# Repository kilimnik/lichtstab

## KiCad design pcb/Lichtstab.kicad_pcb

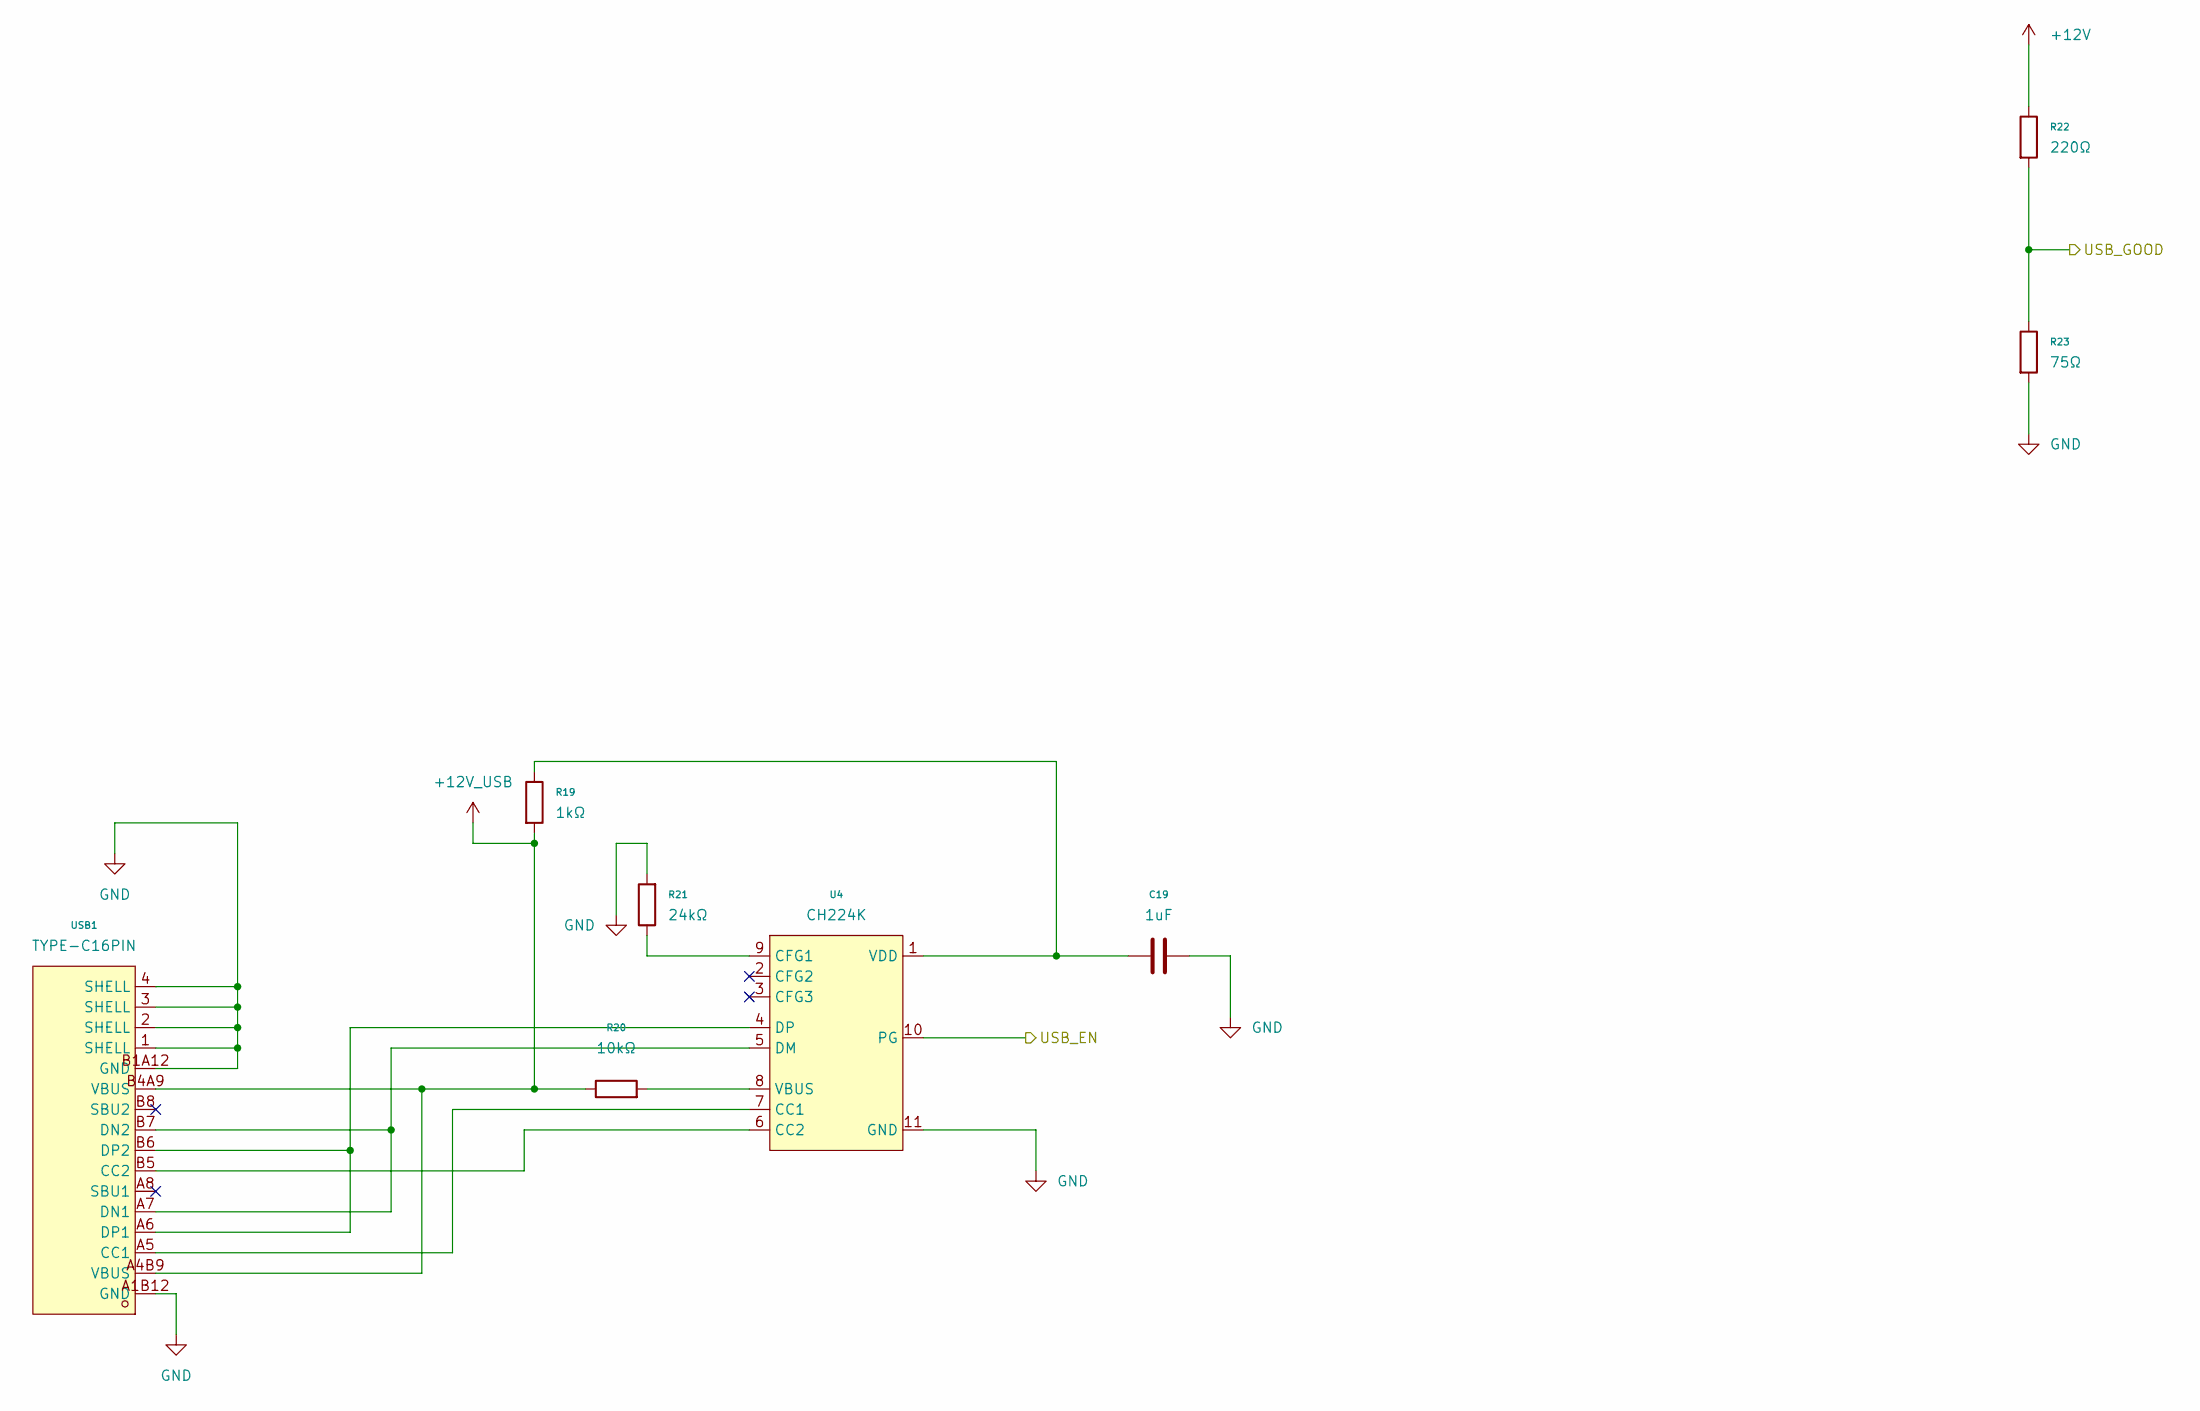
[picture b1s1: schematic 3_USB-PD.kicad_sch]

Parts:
C19: 1uF; C_0805_2012Metric; LCSC C28323
R19: 1kΩ; R_0603_1608Metric; LCSC C21190
R20: 10kΩ; R_0603_1608Metric; LCSC C25804
R21: 24kΩ; R_0603_1608Metric; LCSC C23352
R22: 220Ω; R_0603_1608Metric; LCSC C22962
R23: 75Ω; R_0603_1608Metric; LCSC C4275
U4: CH224K; ESSOP-10_L4.9-W3.9-P1.0-LS6.0-TL-EP; LCSC C970725
USB1: TYPE-C16PIN; USB-C-SMD_TYPE-C16PIN; LCSC C393939

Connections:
+12V: R22.1; also elsewhere on the board
+12V_USB: R19.2, R20.1, USB1.A4B9 (VBUS), USB1.B4A9 (VBUS); also elsewhere on the board
/General/ESP_EN: U4.10 (PG); also elsewhere on the board
/General/USB_GOOD: R22.2, R23.1; also elsewhere on the board
GND: C19.1, R21.2, R23.2, U4.11 (GND), USB1.1 (SHELL), USB1.2 (SHELL), USB1.3 (SHELL), USB1.4 (SHELL), USB1.A1B12 (GND), USB1.B1A12 (GND); also elsewhere on the board
unnamed: U4.7 (CC1), USB1.A5 (CC1)
unnamed: U4.6 (CC2), USB1.B5 (CC2)
unnamed: R21.1, U4.9 (CFG1)
unnamed: U4.5 (DM), USB1.A7 (DN1), USB1.B7 (DN2)
unnamed: U4.4 (DP), USB1.A6 (DP1), USB1.B6 (DP2)
unnamed: R20.2, U4.8 (VBUS)
unnamed: C19.2, R19.1, U4.1 (VDD)

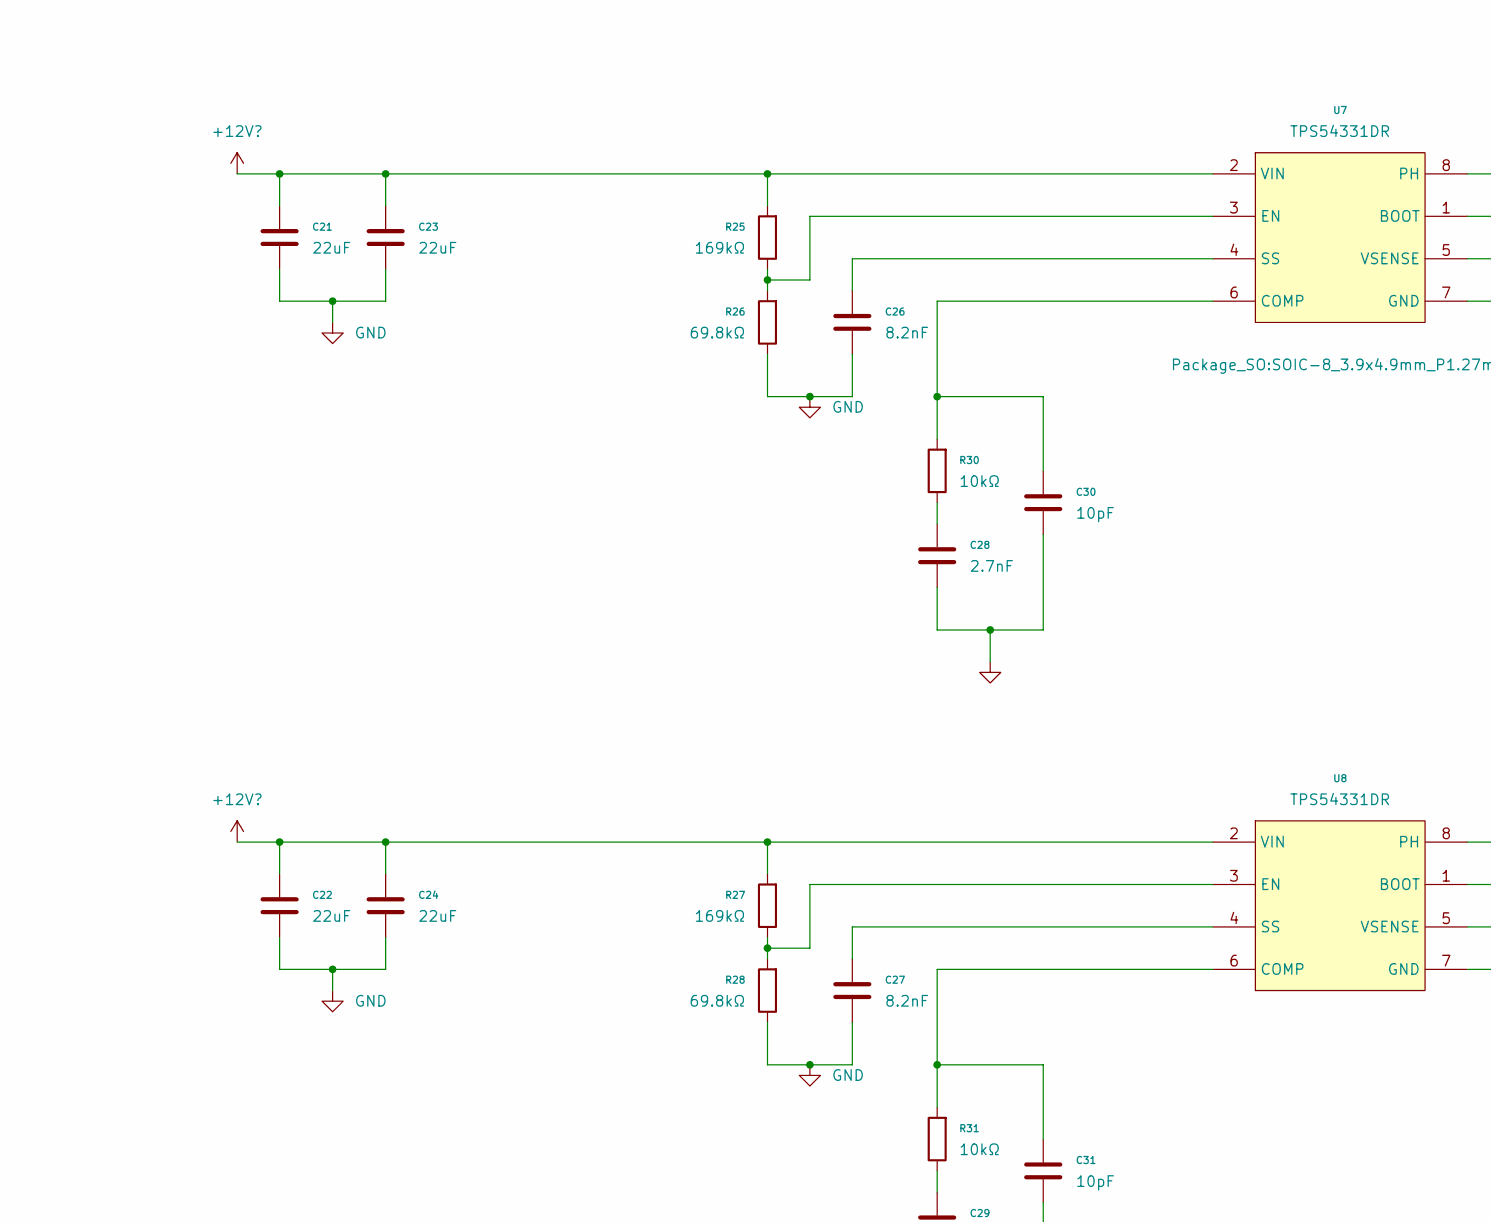
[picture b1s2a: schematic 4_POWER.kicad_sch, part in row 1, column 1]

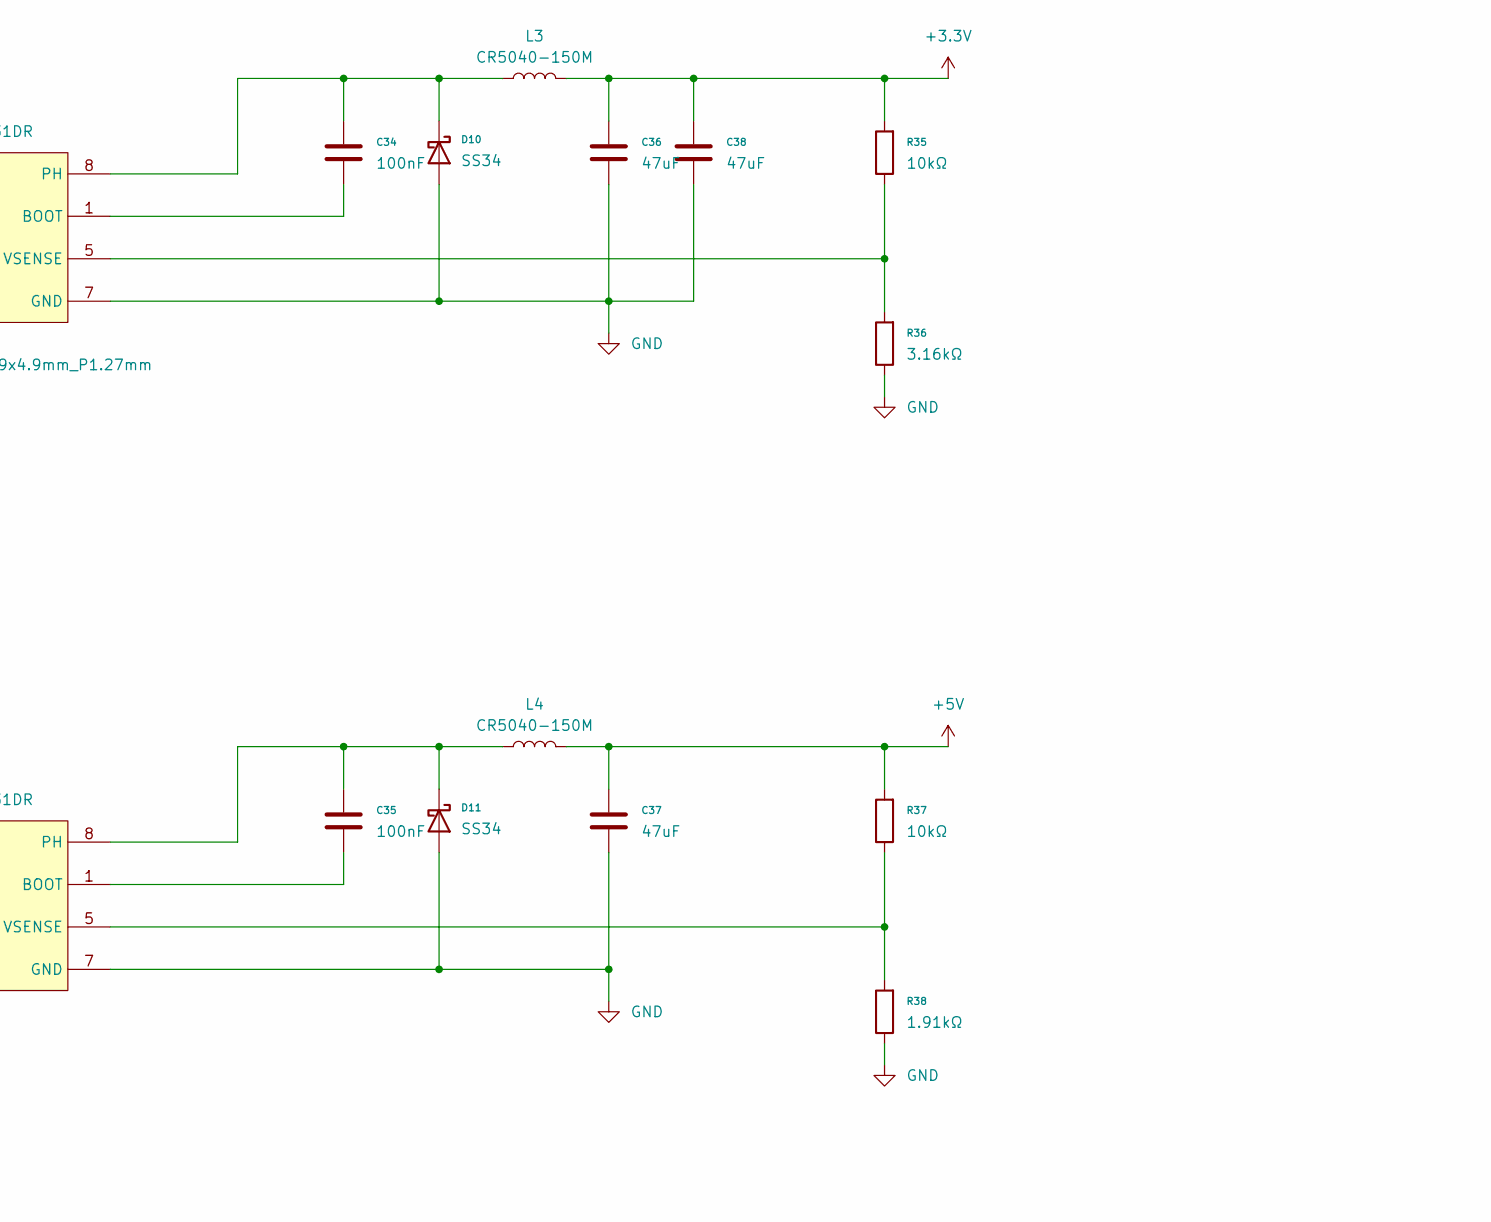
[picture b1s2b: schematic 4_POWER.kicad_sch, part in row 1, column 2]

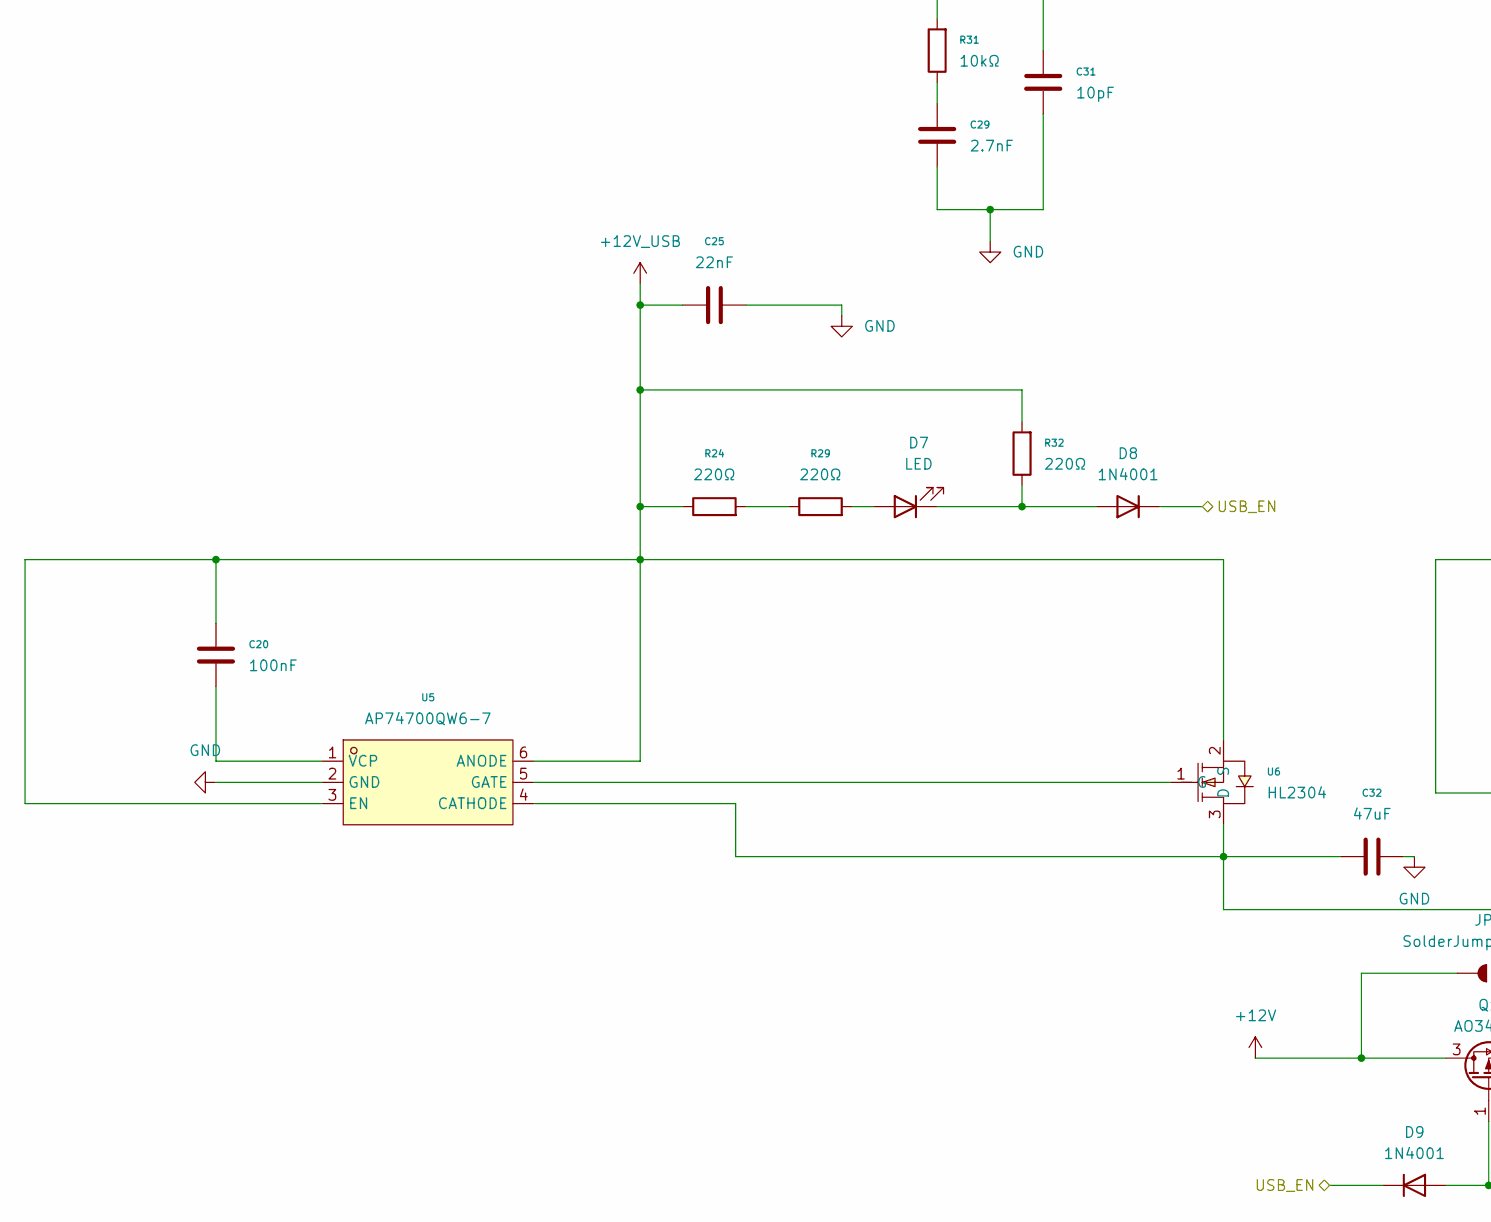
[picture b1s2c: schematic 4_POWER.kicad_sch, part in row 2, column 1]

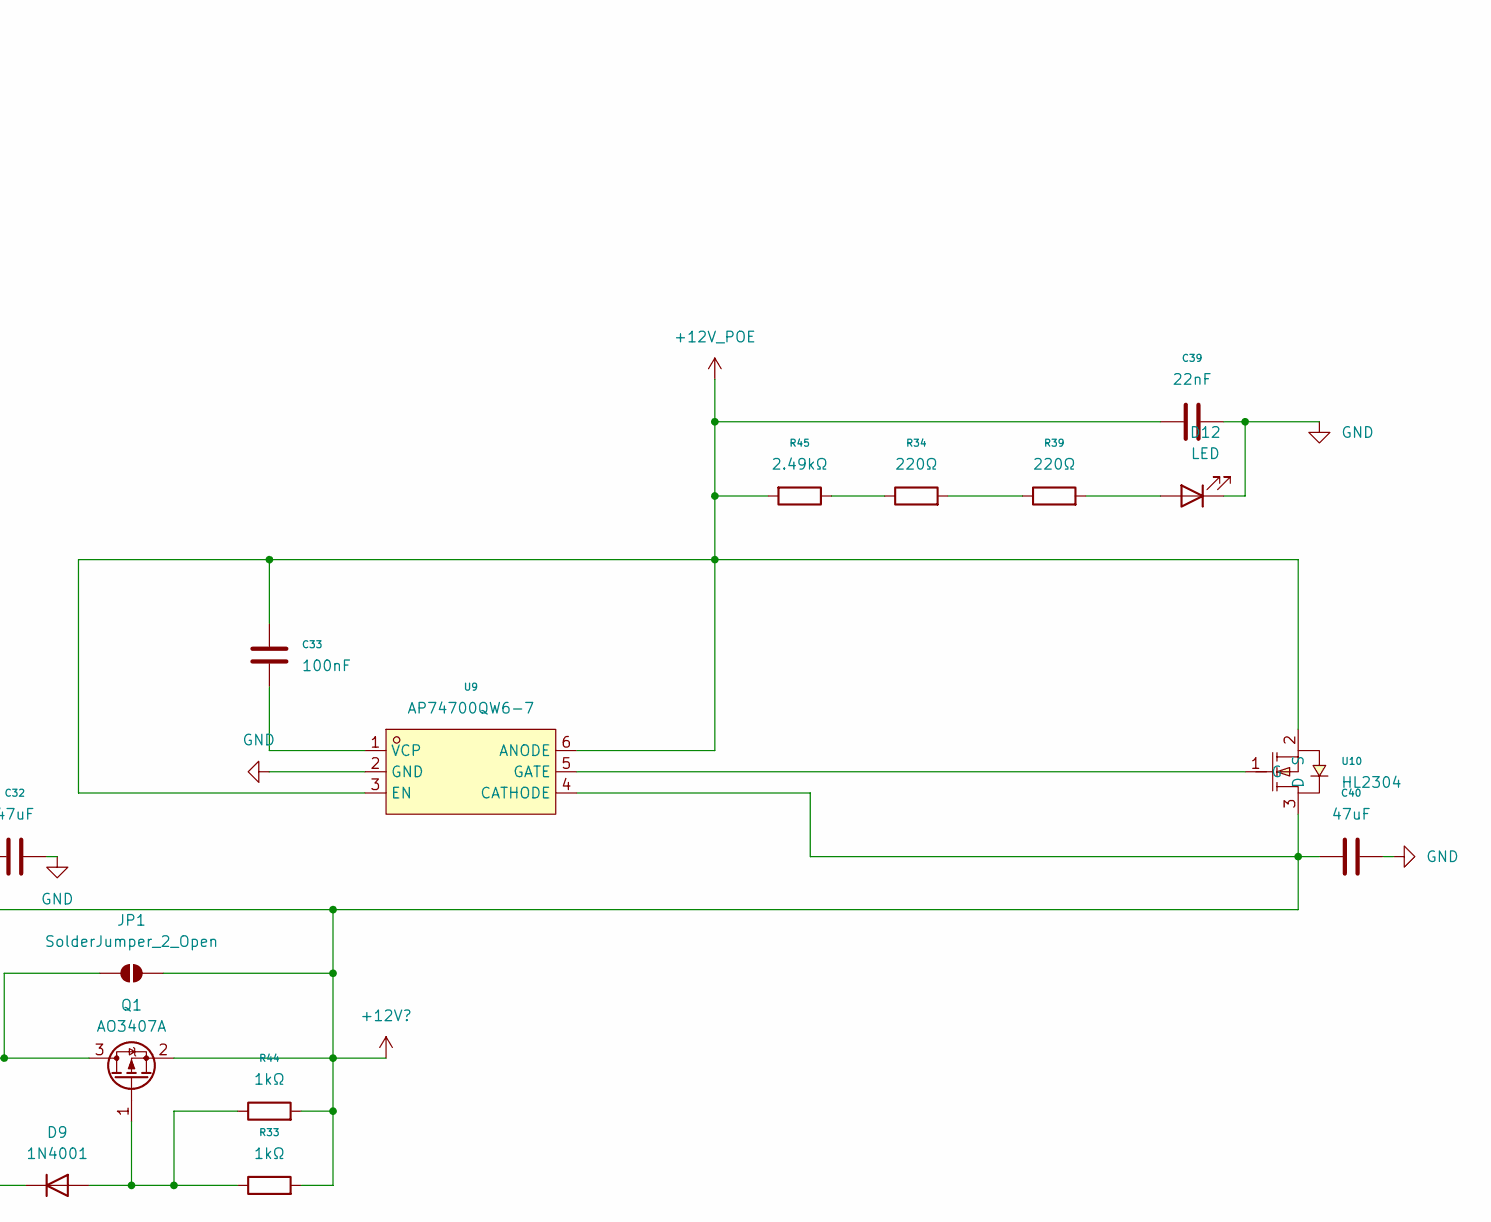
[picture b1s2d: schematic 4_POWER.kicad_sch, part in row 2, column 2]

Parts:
C20, C33, C34, C35: 100nF; C_0603_1608Metric; LCSC C14663
C21, C22, C23, C24: 22uF; C_1210_3225Metric; LCSC C2918506
C25, C39: 22nF; C_0603_1608Metric; LCSC C21122
C26, C27: 8.2nF; C_0603_1608Metric; LCSC C1322360
C28, C29: 2.7nF; C_0805_2012Metric; LCSC C5186791
C30, C31: 10pF; C_0805_2012Metric; LCSC C157608
C32, C36, C37, C38, C40: 47uF; C_1206_3216Metric; LCSC C22367835
D7, D12: LED; LED_0805_2012Metric; LCSC C2297
D8, D9: 1N4001; D_SOD-123F; LCSC C2892326
D10, D11: SS34; D_SMA; LCSC C8678
JP1: SolderJumper_2_Open; SolderJumper-2_P1.3mm_Open_TrianglePad1.0x1.5mm
L3, L4: CR5040-150M; IND-SMD_L5.0-W5.0_SWPA5040S; LCSC Part C520353
Q1: AO3407A; SOT-23; LCSC C347478
R24, R29, R32, R34, R39: 220Ω; R_0603_1608Metric; LCSC C22962
R25, R27: 169kΩ; R_0603_1608Metric; LCSC C22817
R26, R28: 69.8kΩ; R_0603_1608Metric; LCSC C23098
R30, R31, R35, R37: 10kΩ; R_0603_1608Metric; LCSC C25804
R33, R44: 1kΩ; R_0603_1608Metric; LCSC C21190
R36: 3.16kΩ; R_0603_1608Metric; LCSC C22993
R38: 1.91kΩ; R_0603_1608Metric; LCSC C22853
R45: 2.49kΩ; R_0603_1608Metric; LCSC C22908
U5, U9: AP74700QW6-7; SOT-23-6; LCSC C5381661
U6, U10: HL2304; SOT-23; LCSC C7420346
U7, U8: TPS54331DR; SOIC-8_3.9x4.9mm_P1.27mm; LCSC C9865

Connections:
+3.3V: C36.1, C38.1, L3.2, R35.2; also elsewhere on the board
+5V: C37.2, L4.2, R37.2; also elsewhere on the board
+12V: JP1.1 (A), Q1.3 (D); also elsewhere on the board
+12V?: C21.2, C22.2, C23.2, C24.2, C32.1, C40.1, JP1.2 (B), Q1.2 (S), R25.2, R27.2, R33.2, R44.2, U5.4 (CATHODE), U6.3 (D), U7.2 (VIN), U8.2 (VIN), U9.4 (CATHODE), U10.3 (D)
+12V_POE: C33.1, C39.1, R45.2, U9.3 (EN), U9.6 (ANODE), U10.2 (S); also elsewhere on the board
+12V_USB: C20.1, C25.1, R24.1, R32.2, U5.3 (EN), U5.6 (ANODE), U6.2 (S); also elsewhere on the board
/General/ESP_EN: D8.1 (K), D9.1 (K); also elsewhere on the board
GND: C21.1, C22.1, C23.1, C24.1, C25.2, C26.1, C27.1, C28.1, C29.1, C30.1, C31.1, C32.2, C36.2, C37.1, C38.2, C39.2, C40.2, D10.2 (A), D11.2 (A), D12.1 (K), R26.1, R28.1, R36.1, R38.1, U5.2 (GND), U7.7 (GND), U8.7 (GND), U9.2 (GND); also elsewhere on the board
unnamed: C28.2, R30.1
unnamed: C29.2, R31.1
unnamed: D7.2 (A), R29.2
unnamed: D7.1 (K), D8.2 (A), R32.1
unnamed: D9.2 (A), Q1.1 (G), R33.1, R44.1
unnamed: C34.1, D10.1 (K), L3.1, U7.8 (PH)
unnamed: C35.1, D11.1 (K), L4.1, U8.8 (PH)
unnamed: D12.2 (A), R39.2
unnamed: R24.2, R29.1
unnamed: R34.1, R45.1
unnamed: R34.2, R39.1
unnamed: U5.5 (GATE), U6.1 (G)
unnamed: C20.2, U5.1 (VCP)
unnamed: C34.2, U7.1 (BOOT)
unnamed: C30.2, R30.2, U7.6 (COMP)
unnamed: R25.1, R26.2, U7.3 (EN)
unnamed: C26.2, U7.4 (SS)
unnamed: R35.1, R36.2, U7.5 (VSENSE)
unnamed: C35.2, U8.1 (BOOT)
unnamed: C31.2, R31.2, U8.6 (COMP)
unnamed: R27.1, R28.2, U8.3 (EN)
unnamed: C27.2, U8.4 (SS)
unnamed: R37.1, R38.2, U8.5 (VSENSE)
unnamed: C33.2, U9.1 (VCP)
unnamed: U9.5 (GATE), U10.1 (G)

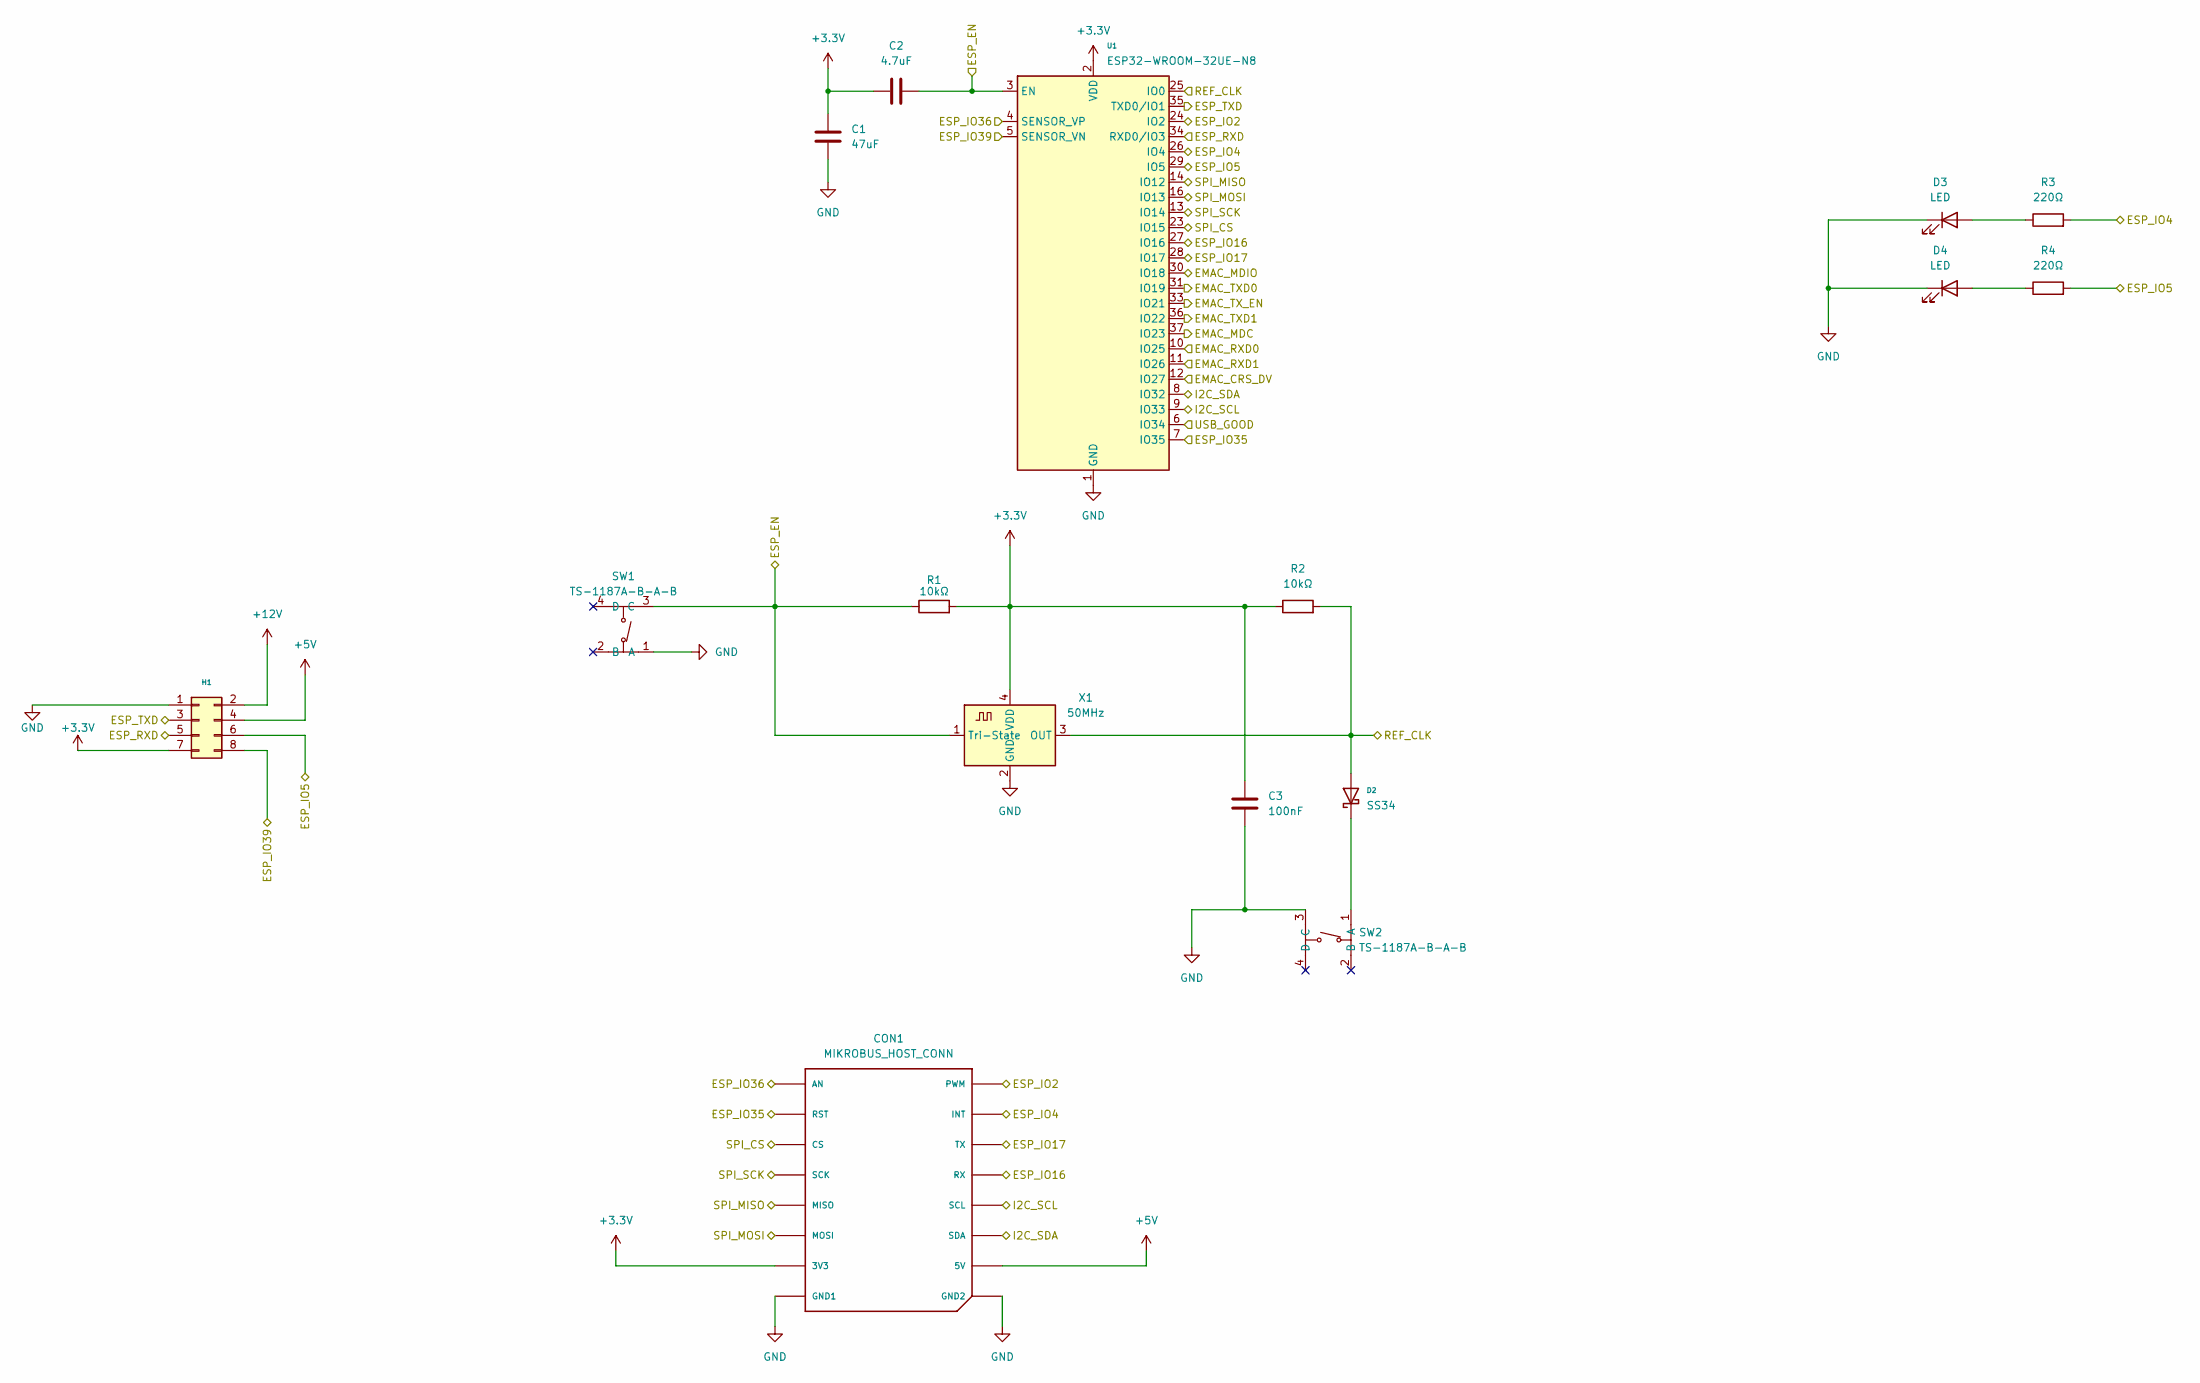
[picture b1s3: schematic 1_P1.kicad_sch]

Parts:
C1: 47uF; C_1206_3216Metric; LCSC C22367835
C2: 4.7uF; C_0603_1608Metric
C3: 100nF; C_0603_1608Metric
CON1: MIKROBUS_HOST_CONN
D2: SS34; D_SMA; LCSC C8678
D3, D4: LED; LED_0805_2012Metric; LCSC C34499
H1: PinHeader_2x04_P2.54mm_Vertical_SMD; Manufacturer Part Programming Header; LCSC C192300
R1, R2: 10kΩ; R_0603_1608Metric
R3, R4: 220Ω; R_0603_1608Metric
SW1: TS-1187A-B-A-B; SW-SMD_4P-L5.1-W5.1-P3.70-LS6.5-TL-2; Manufacturer Part Reset Switch; LCSC C318884
SW2: TS-1187A-B-A-B; SW-SMD_4P-L5.1-W5.1-P3.70-LS6.5-TL-2; Manufacturer Part Boot Switch; LCSC C318884
U1: ESP32-WROOM-32UE-N8; ESP32-WROOM-32UE; LCSC C701345
X1: 50MHz; Crystal_SMD_3225-4Pin_3.2x2.5mm; LCSC C717684

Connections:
+3.3V: C1.1, C2.2, C3.1, CON1.P7 (3V3), H1.7, R1.2, R2.1, U1.2 (VDD), X1.4 (VDD); also elsewhere on the board
+5V: CON1.P10 (5V), H1.4; also elsewhere on the board
+12V: H1.2; also elsewhere on the board
/General/EMAC_CRS_DV: U1.12 (IO27); also elsewhere on the board
/General/EMAC_MDC: U1.37 (IO23); also elsewhere on the board
/General/EMAC_MDIO: U1.30 (IO18); also elsewhere on the board
/General/EMAC_RXD0: U1.10 (IO25); also elsewhere on the board
/General/EMAC_RXD1: U1.11 (IO26); also elsewhere on the board
/General/EMAC_TXD0: U1.31 (IO19); also elsewhere on the board
/General/EMAC_TXD1: U1.36 (IO22); also elsewhere on the board
/General/EMAC_TX_EN: U1.33 (IO21); also elsewhere on the board
/General/ESP_EN: C2.1, R1.1, SW1.3 (C), U1.3 (EN), X1.1 (Tri-State); also elsewhere on the board
/General/ESP_IO2: CON1.P16 (PWM), U1.24 (IO2); also elsewhere on the board
/General/ESP_IO4: CON1.P15 (INT), R3.2, U1.26 (IO4); also elsewhere on the board
/General/ESP_IO5: H1.6, R4.2, U1.29 (IO5); also elsewhere on the board
/General/ESP_IO16: CON1.P13 (RX), U1.27 (IO16); also elsewhere on the board
/General/ESP_IO17: CON1.P14 (TX), U1.28 (IO17); also elsewhere on the board
/General/ESP_IO35: CON1.P2 (RST), U1.7 (IO35); also elsewhere on the board
/General/ESP_IO36: CON1.P1 (AN), U1.4 (SENSOR_VP); also elsewhere on the board
/General/ESP_IO39: H1.8, U1.5 (SENSOR_VN); also elsewhere on the board
/General/ESP_RXD: H1.5, U1.34 (RXD0/IO3)
/General/ESP_TXD: H1.3, U1.35 (TXD0/IO1)
/General/I2C_SCL: CON1.P12 (SCL), U1.9 (IO33); also elsewhere on the board
/General/I2C_SDA: CON1.P11 (SDA), U1.8 (IO32); also elsewhere on the board
/General/REF_CLK: D2.2 (A), R2.2, U1.25 (IO0), X1.3 (OUT); also elsewhere on the board
/General/SPI_CS: CON1.P3 (CS), U1.23 (IO15); also elsewhere on the board
/General/SPI_MISO: CON1.P5 (MISO), U1.14 (IO12); also elsewhere on the board
/General/SPI_MOSI: CON1.P6 (MOSI), U1.16 (IO13); also elsewhere on the board
/General/SPI_SCK: CON1.P4 (SCK), U1.13 (IO14); also elsewhere on the board
/General/USB_GOOD: U1.6 (IO34); also elsewhere on the board
GND: C1.2, C3.2, CON1.P8 (GND1), CON1.P9 (GND2), D3.1 (K), D4.1 (K), H1.1, SW1.1 (A), SW2.3 (C), U1.1 (GND), U1.15 (GND), U1.38 (GND), U1.39 (GND), X1.2 (GND); also elsewhere on the board
unnamed: D2.1 (K), SW2.1 (A)
unnamed: D3.2 (A), R3.1
unnamed: D4.2 (A), R4.1

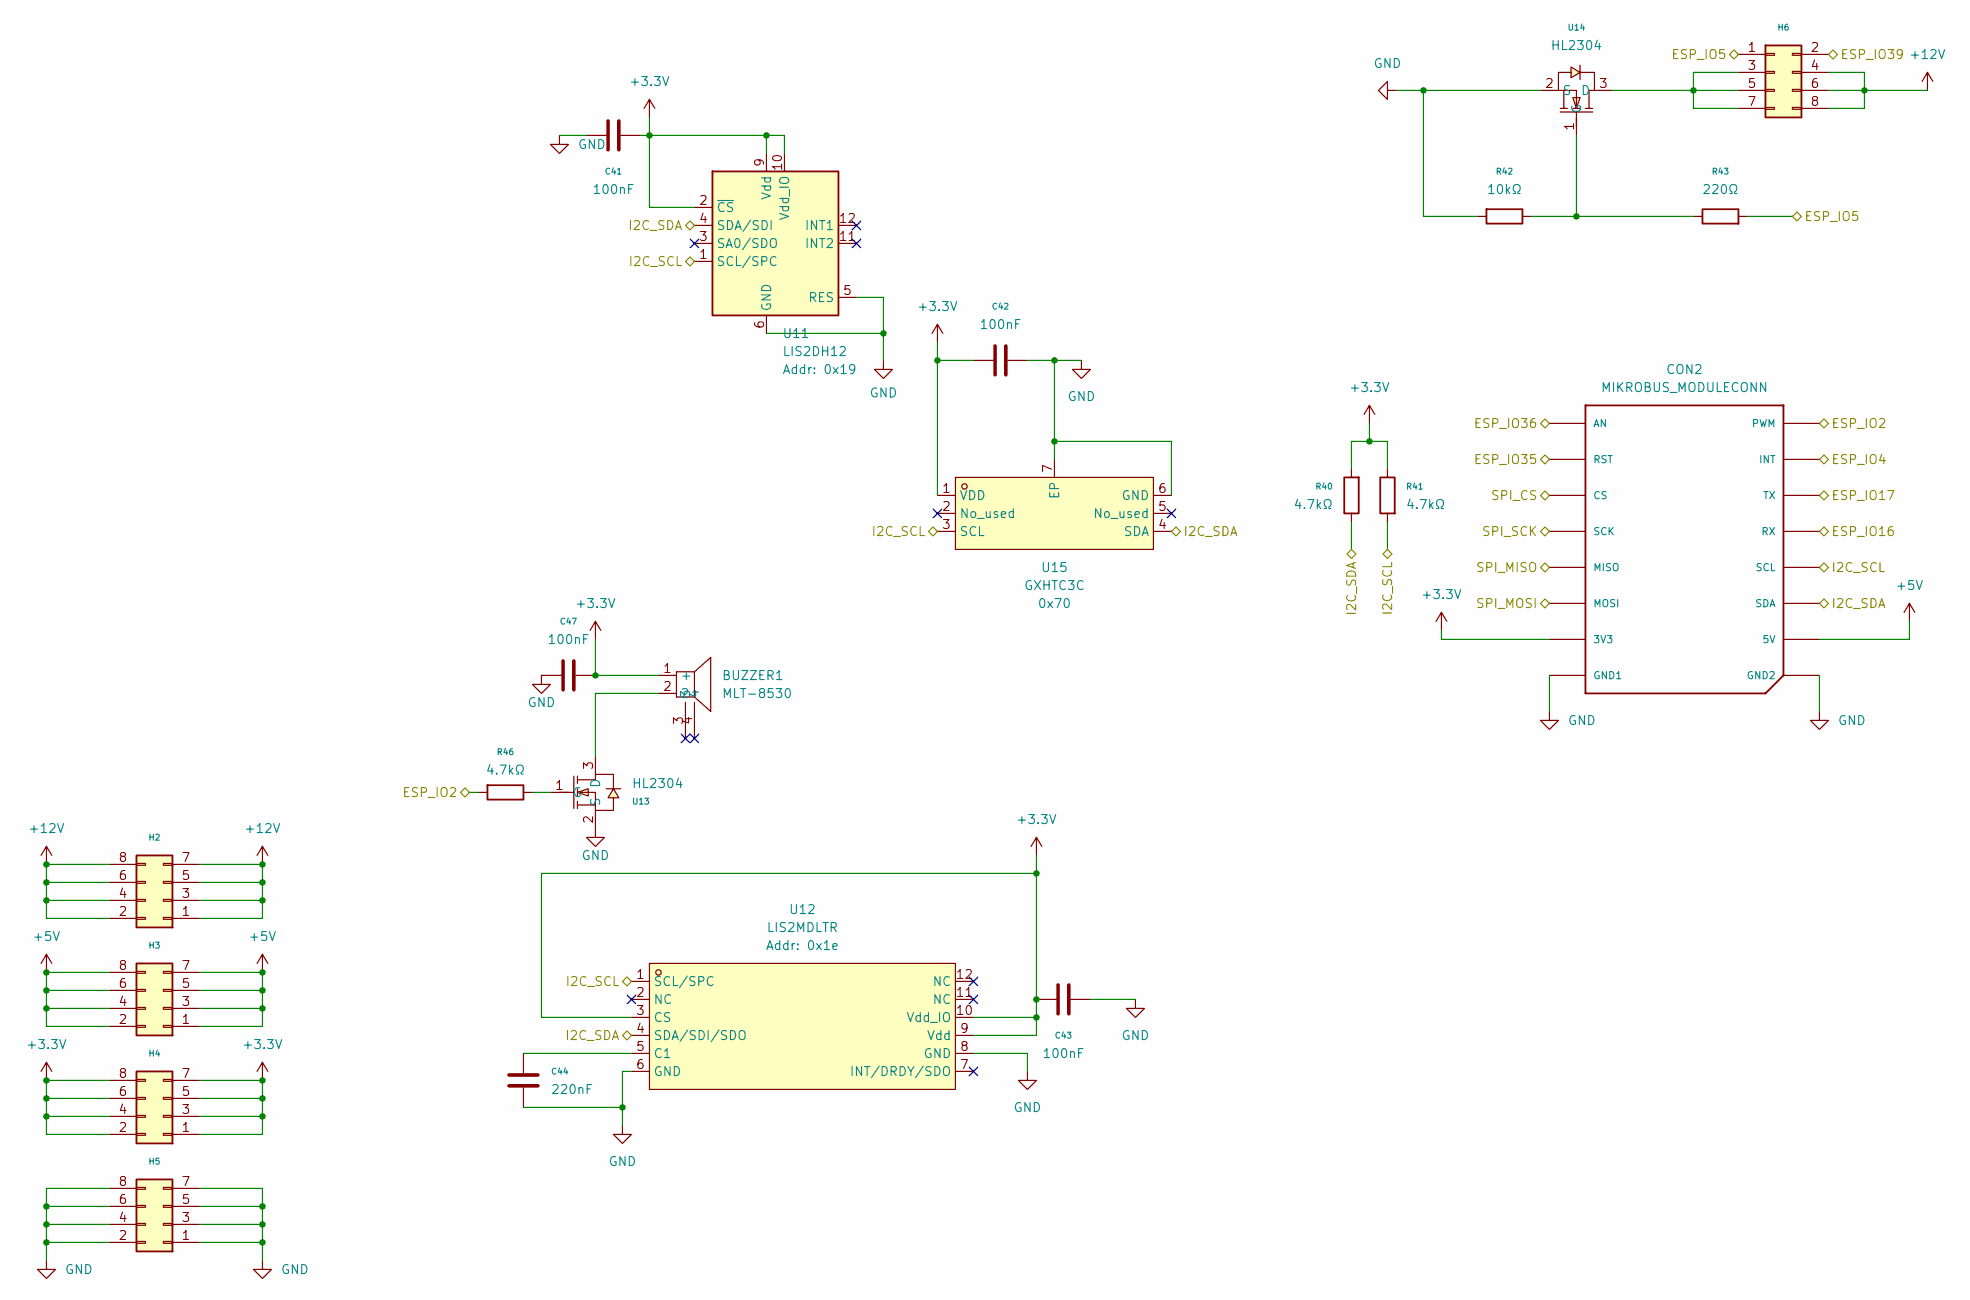
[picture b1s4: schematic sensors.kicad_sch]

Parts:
BUZZER1: MLT-8530; BUZ-SMD_4P-L8.5-W8.5-P8.50-BR; LCSC Part C94599
C41, C42, C43, C47: 100nF; C_0603_1608Metric; LCSC C14663
C44: 220nF; C_0603_1608Metric
CON2: MIKROBUS_MODULECONN; MIKROBUS_MODULE_CONN
H2: 2.54-2*4P立贴针; PinHeader_2x04_P2.54mm_Vertical_SMD; Manufacturer Part 12V Header; LCSC C192300
H3, H4: 2.54-2*4P立贴针; PinHeader_2x04_P2.54mm_Vertical_SMD; Manufacturer Part 3.3V Header; LCSC C192300
H5: 2.54-2*4P立贴针; PinHeader_2x04_P2.54mm_Vertical_SMD; Manufacturer Part GND Header; LCSC C192300
H6: 2.54-2*4P立贴针; PinHeader_2x04_P2.54mm_Vertical_SMD; Manufacturer Part Light Header; LCSC C192300
R40, R41, R46: 4.7kΩ; R_0603_1608Metric; LCSC C23162
R42: 10kΩ; R_0603_1608Metric; LCSC C25804
R43: 220Ω; R_0603_1608Metric; LCSC C22962
U11: LIS2DH12; LGA-12_2x2mm_P0.5mm; LCSC C110926
U12: LIS2MDLTR; LGA-12_L2.0-W2.0-P0.50-BL; LCSC C919695
U13, U14: HL2304; SOT-23; LCSC C7420346
U15: GXHTC3C; DFN-6_L2.0-W2.0-P0.50-TL-EP; LCSC Part C2913568

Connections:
+3.3V: BUZZER1.1 (+), C41.1, C42.2, C43.1, C47.1, CON2.P7 (3V3), H4.1, H4.2, H4.3, H4.4, H4.5, H4.6, H4.7, H4.8, R40.2, R41.1, U11.2 (~CS), U11.9 (Vdd), U11.10 (Vdd_IO), U12.3 (CS), U12.9 (Vdd), U12.10 (Vdd_IO), U15.1 (VDD); also elsewhere on the board
+5V: CON2.P10 (5V), H3.1, H3.2, H3.3, H3.4, H3.5, H3.6, H3.7, H3.8; also elsewhere on the board
+12V: H2.1, H2.2, H2.3, H2.4, H2.5, H2.6, H2.7, H2.8, H6.4, H6.6, H6.8; also elsewhere on the board
/General/ESP_IO2: CON2.P16 (PWM), R46.2; also elsewhere on the board
/General/ESP_IO4: CON2.P15 (INT); also elsewhere on the board
/General/ESP_IO5: H6.1, R43.2; also elsewhere on the board
/General/ESP_IO16: CON2.P13 (RX); also elsewhere on the board
/General/ESP_IO17: CON2.P14 (TX); also elsewhere on the board
/General/ESP_IO35: CON2.P2 (RST); also elsewhere on the board
/General/ESP_IO36: CON2.P1 (AN); also elsewhere on the board
/General/ESP_IO39: H6.2; also elsewhere on the board
/General/I2C_SCL: CON2.P12 (SCL), R41.2, U11.1 (SCL/SPC), U12.1 (SCL/SPC), U15.3 (SCL); also elsewhere on the board
/General/I2C_SDA: CON2.P11 (SDA), R40.1, U11.4 (SDA/SDI), U12.4 (SDA/SDI/SDO), U15.4 (SDA); also elsewhere on the board
/General/SPI_CS: CON2.P3 (CS); also elsewhere on the board
/General/SPI_MISO: CON2.P5 (MISO); also elsewhere on the board
/General/SPI_MOSI: CON2.P6 (MOSI); also elsewhere on the board
/General/SPI_SCK: CON2.P4 (SCK); also elsewhere on the board
GND: C41.2, C42.1, C43.2, C44.1, C47.2, CON2.P8 (GND1), CON2.P9 (GND2), H5.1, H5.2, H5.3, H5.4, H5.5, H5.6, H5.7, H5.8, R42.2, U11.5 (RES), U11.6 (GND), U11.7 (GND), U11.8 (GND), U12.6 (GND), U12.8 (GND), U13.2 (S), U14.2 (S), U15.6 (GND), U15.7 (EP); also elsewhere on the board
unnamed: H6.3, H6.5, H6.7, U14.3 (D)
unnamed: C44.2, U12.5 (C1)
unnamed: BUZZER1.2, U13.3 (D)
unnamed: R46.1, U13.1 (G)
unnamed: R42.1, R43.1, U14.1 (G)
